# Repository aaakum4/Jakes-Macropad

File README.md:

# Gojopad
GojoPad is a fully 3D-printed 4-key macropad featuring a rotary encoder, a small OLED display, and a single RGB LED, named after the 1mm-deep Gojo etching on its surface. Its firmware provides dynamic media, voice chat, and display control, making it both functional and visually engaging.

## Features
- Fully 3D-printed dual-layer case with a 2° ergonomic tilt. Printed in white filament to match Gojo's hair and my white setup.
- 128x32 OLED display showing multiple modes: uptime clock, custom mode label, simple graphic, and volume bar.
- EC11 rotary encoder:
-   Rotate clockwise to increase volume, counterclockwise to decrease volume.
-   Push to toggle mute.
- 5 programmable keys:
-   SW1: cycle OLED display modes
-   W2: next track
-   SW3: previous track
-   SW4: voice chat toggle
-   SW5: play/pause
-   2 SK6812 MINI-E LEDs: red when muted, blue when unmuted.
-   KMK firmware support for full macro and input customization.

## CAD Model
The case is composed of two 3D-printed pieces:
Base: secures the PCB and provides structural support and sits on a roughly 2˚ tilt.
Top housing: holds switches, diffuses LED light, and features the Gojo etching.
* Printed in white filament to match Gojo's hair and my white setup.

Assembly uses 4 M3 screws with heatset inserts.

How it will fit together:

## PCB
The PCB is designed in KiCad with MX-style switch footprints and supports future enhancements like a ground plane.

Schematic:

PCB Layout:

## Firmware Overview

GojoPad runs KMK firmware:
- Rotary encoder adjusts volume in 5% steps, push toggles mute.
- OLED cycles through four modes: uptime clock, custom label, simple graphic, and volume bar.
- Keys handle media control, voice chat toggle, and OLED mode cycling.
- NeoPixel LED reflects mute state (red = muted, blue = unmuted).

## BOM (Bill of Materials)
- 4x Cherry MX switches
- 4x Keycaps (DSA recommended)
- 4x M3x5mx4mm heatset inserts
- 4x M3x16mm screws
- 2x SK6812 MINI-E LEDs
- 1x 0.91" 128x32 OLED display
- 1x EC11 rotary encoder
- 1x XIAO RP2040
- Case: 3D-printed parts

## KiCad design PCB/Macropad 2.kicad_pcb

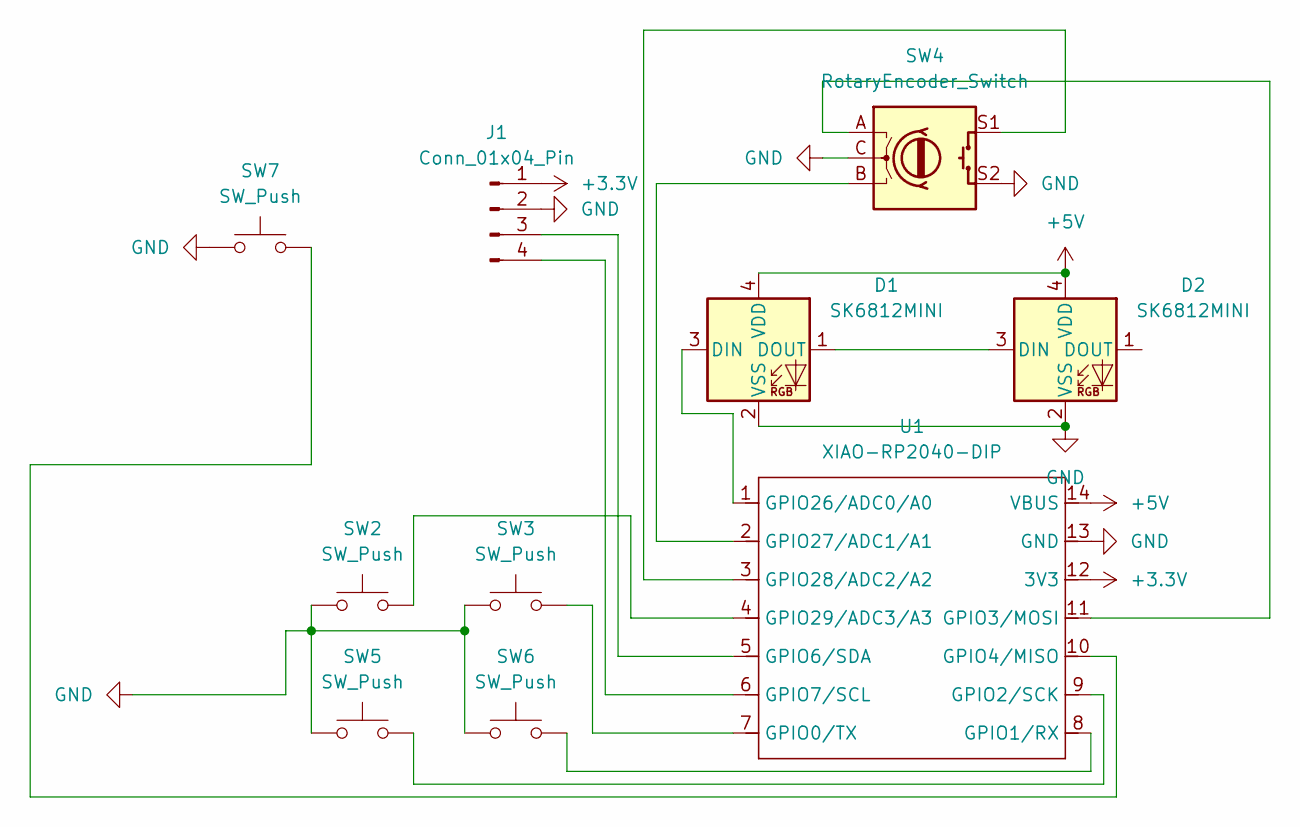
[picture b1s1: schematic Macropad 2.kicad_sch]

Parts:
D1, D2: SK6812MINI; LED_SK6812MINI_PLCC4_3.5x3.5mm_P1.75mm
J1: Conn_01x04_Pin; SSD1306-0.91-OLED-4pin-128x32
SW2, SW3, SW5, SW6, SW7: SW_Push; SW_Cherry_MX_1.00u_PCB
SW4: RotaryEncoder_Switch; RotaryEncoder_Alps_EC11E-Switch_Vertical_H20mm
U1: XIAO-RP2040-DIP

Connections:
+3.3V: J1.1, U1.12 (3V3)
+5V: D1.4 (VDD), D2.4 (VDD), U1.14 (VBUS)
GND: D1.2 (VSS), D2.2 (VSS), J1.2, SW2.1, SW3.1, SW4.C, SW4.S2, SW5.1, SW6.1, SW7.1, U1.13 (GND)
unnamed: D1.3 (DIN), U1.1 (GPIO26/ADC0/A0)
unnamed: D1.1 (DOUT), D2.3 (DIN)
unnamed: J1.3, U1.5 (GPIO6/SDA)
unnamed: J1.4, U1.6 (GPIO7/SCL)
unnamed: SW3.2, U1.7 (GPIO0/TX)
unnamed: SW6.2, U1.8 (GPIO1/RX)
unnamed: SW5.2, U1.9 (GPIO2/SCK)
unnamed: SW4.A, U1.11 (GPIO3/MOSI)
unnamed: SW7.2, U1.10 (GPIO4/MISO)
unnamed: SW4.B, U1.2 (GPIO27/ADC1/A1)
unnamed: SW4.S1, U1.3 (GPIO28/ADC2/A2)
unnamed: SW2.2, U1.4 (GPIO29/ADC3/A3)

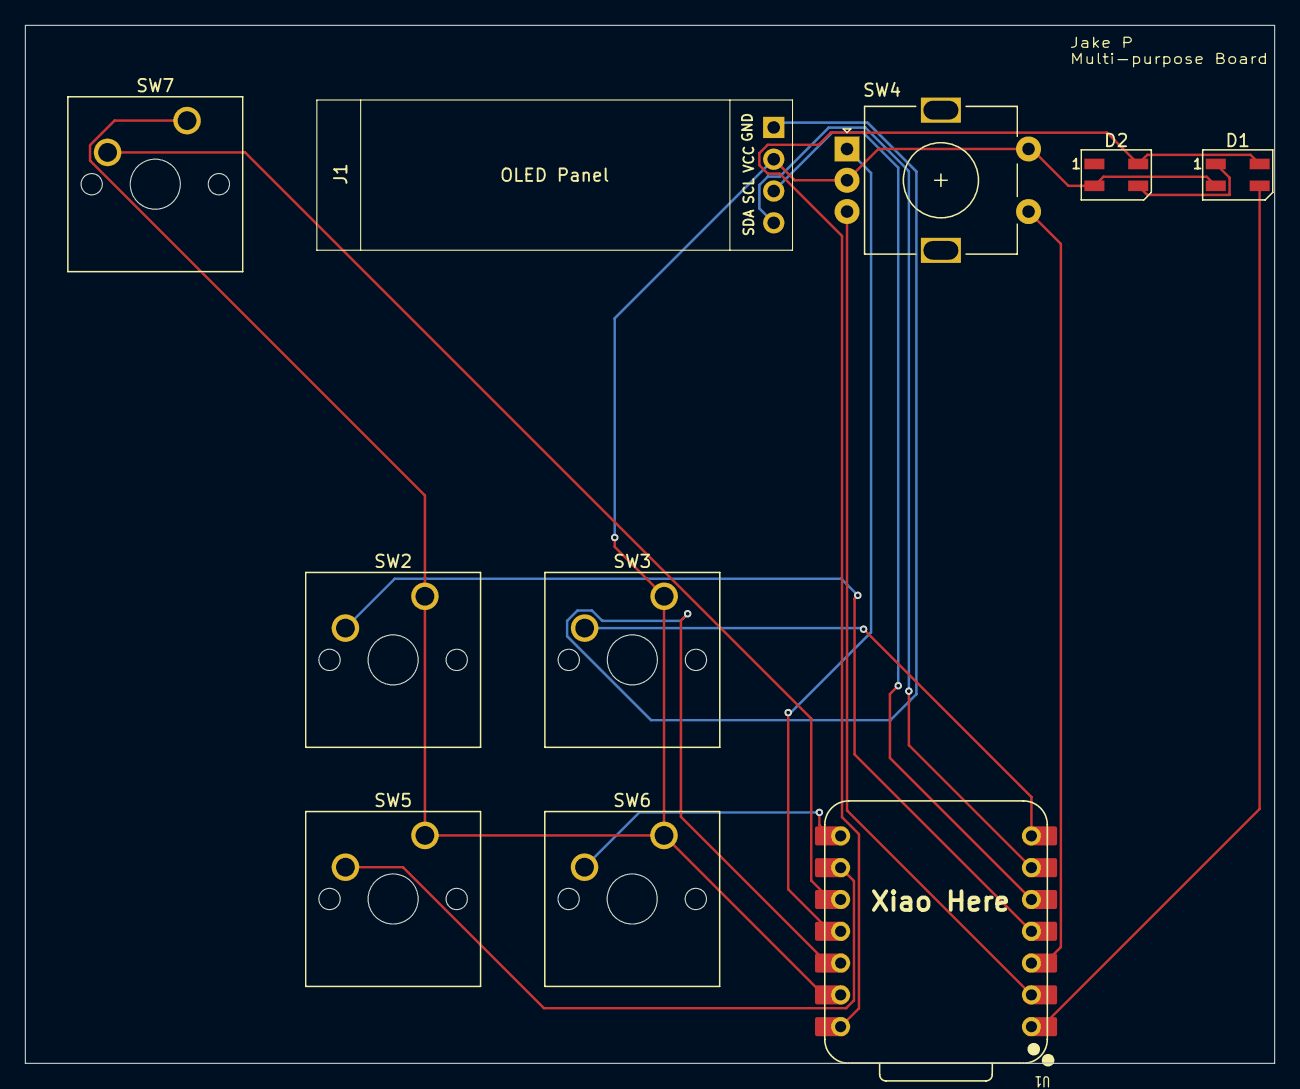
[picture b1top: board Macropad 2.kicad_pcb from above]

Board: 2 copper layers, 99.8 x 82.9 mm, 10 parts (0 on the bottom side), 15 nets.

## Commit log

2025-12-05 Added CAD files
2025-12-05 Create Firmware
2025-12-05 Add initial README with project title
2025-12-05 Expand README with GojoPad details
    Added detailed description of GojoPad features, CAD model, PCB design, firmware overview, and BOM.
2025-12-05 Add PCB schematic and layout images to README
2025-12-05 Update BOM to specify Cherry MX switches
2025-12-05 Updated Code
2025-12-05 Update assembly instructions and add fitting details
    Removed mention of stability in assembly instructions and added a section on how the pieces fit together with an image.
2025-12-05 Enhance README with filament color information
    Added detail about the filament color used for printing.
